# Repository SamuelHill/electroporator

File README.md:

# Electroporator PCB

Various PCB designs for a simple, versatile, and inexpensive electroporator. Inspiration and original design from [T. Bullman, et. al. 2015](https://onlinelibrary.wiley.com/doi/10.1111/dgd.12216). As stated in the paper:

> Electroporation is a useful technique to study gene function during development but its broad application is hampered due to the expensive equipment needed.

While I agree with this and the rest of the paper largely, I believe the design set forth is both cluttered and unnecessarily complicated. This is mainly due to the use of a breadboard (or PCB breadboard), and given the current capabilities and price point of manufacturing a custom PCB this seems the obvious place to start for simplification. To that end, I designed a simple PCB that also contains much of the needed information for construction and operation on the silkscreen. After successfully implementing and using the v.0 system, I also designed and am working on implementing a handful of v.1 boards.

The layout of this project is a series of nested KiCad projects for easy navigation within KiCad. To better show the functionality of the HE721A IC's - and add this product and footprint - I created a custom part (found in the parts folder). In the gerber folder is the compiled output of the v.0 board which has been printed, tested, and used successfully. As more of the designs are tested I will add more completed gerber files. The archive folder can be ignored as it just includes some attempts at having the LED output on the electrode side of the circuit. The v0 and v1 folders contain the designs for each version and v1 contains a number of modifications that are discussed later in this readme.

## Breadboard layout

To make sure I had the circuit correct and that my parts were compatible I did a test on a breadboard just as the paper laid out.

Breadboard build:

Testing with oscilloscope:

Sizing up PCB from breadboard layout:

## V.0 Design

Below are 2D and 3D renders of the v.0 design:

This board uses the same layout as the breadboard in terms of components and connections, but - due to the nature of PCBs - doesn't require extra wiring. While the parts listed in the paper are mostly generic and easy to come by such as the resistors, capacitors, and 555 timer, the reed relay is definitely a bit more of an unusual component. While not very expensive for the kind used here, it is unlikely you have a compatible IC lying around. Also, this is another change from the paper - albeit minor - in that the PCB is only designed for reed relays and not miniature latching relays. In addition to using reed relays, I am expecting a relay with diode protection. The relays I used for my testing and builds were [HE721A0510's](https://www.mouser.com/ProductDetail/Littelfuse/HE721A0510?qs=X8LBAgEWIKIfZjBxMXqqBA%3D%3D).

## V.1 Designs *(ordered components on wait lists - _IN PROGRESS & UNTESTED_)*

The v.0 system is reasonably simple and flexible (mostly due to the standard hole spacing for various IO connection types), but there are a few improvements I have thought of while building several v.0 electroporators. To start, all v.1 PCBs do not have a switch in the electrode side of the circuit as this was confusing and seems redundant. From here, I have made a JST connector only version as JST plugs are relatively low profile, dependable, and easy to install once setup. This replaces all screw terminals, buttons and switches, LED indicators, and potentiometer connections with JST plugs - making all IO consistently implemented.

The next v.1 iteration is a JST only copy with a more powerful current regulator in the form of a TL783. While previous versions were limited by the current regulator limitations, this version pushes further into the operational range for the reed relay and allows for pulse voltages from 1.25 to 125V. This opens up the ~45V - 125V range for systems that may require more power. To accommodate the adjust-ability of TL783 for regulating the current (I=Vref/R), R6 was beefed up to allow for radial resistors of appropriate values or a connection to appropriately spec'd potentiometers. These are the only modifications needed as the reed relay and JST connectors can already handle these voltages.

The JST only version could also be considered bloated if you know that your voltage is current regulated. If you were using a lab bench power supply with the current limited, the welding of the reeds in the relay should not be a concern. As such, I made a version with no current regulator for the most simple version of the circuit. This also opens up the full range of up to 200V for the relay so long as your power supply can handle those outputs limited to such low current values.

Lastly, in the interest of pushing the capabilities of this design, I created a kilo-volt version. At somewhere between 5x and 10x more expensive than the HE721, and with a > 1 year lead time, the [SHV05-1A85-78D4K](https://www.mouser.com/ProductDetail/MEDER-electronic-Standex/SHV05-1A85-78D4K?qs=3BE4VKEPqliBgklxw9NVYw%3D%3D) was my choice of overpowered reed relay for this electroporator. In addition to a bigger reed relay (no current regulation like above), the JST connectors won't cut it and have been replaced with kV compatible screw terminals.

## V.0 Implementations

Below are two of the implementations that went to be used in the Hill lab and have been tested on sponge cells. Imaging and further testing is ongoing.

### Large project box

#### Lid:

#### Sides:

#### Lid IO:

#### Sides IO:

#### IO Layout:

This is also the look of the final system (sans LED). The pulse trigger is a tattoo gun pedal so the electrodes can be positioned and operated by the users hands while the trigger can be done with your feet.

#### Power supply:

Yellow & black for 5V, red and black for variable power output...

#### Power IO:

Includes the LED for indicating when the pulse occurs...

IO with wires attached and organized...

Power IO removed from lid for next step...

#### PCB:

Power (5V and electrode variable), electrodes, and the electrode test button wiring...

Power switch, pulse duration potentiometer, and pulse LED indicator control wiring...

All PCB connections in place in box...

Cleaned up the lid wiring...

---

### Small project box

## Results

Using the large project box implementation in the lab with a set of adherent cell electrodes (pictured below):

Sponges (gemules adhered to some variety of 35mm glass bottom petri dish with a micro-well and cover glass) successfully electroporated with plasmids expressing GFP:

## Future work

Development of a SMT line of boards that can be both smaller and more cheaply assembled by the same sorts of PCB manufacturing facilities that allow for the cheaper custom PCBs used in this project. Many PCB production houses have assembly features wherein your board is not only printed but all available components are assembled onto the board for you. While through hole may be easier to do by hand, and is still needed for some IC's like the relay, SMT is cheaper to manufactur and assemble.

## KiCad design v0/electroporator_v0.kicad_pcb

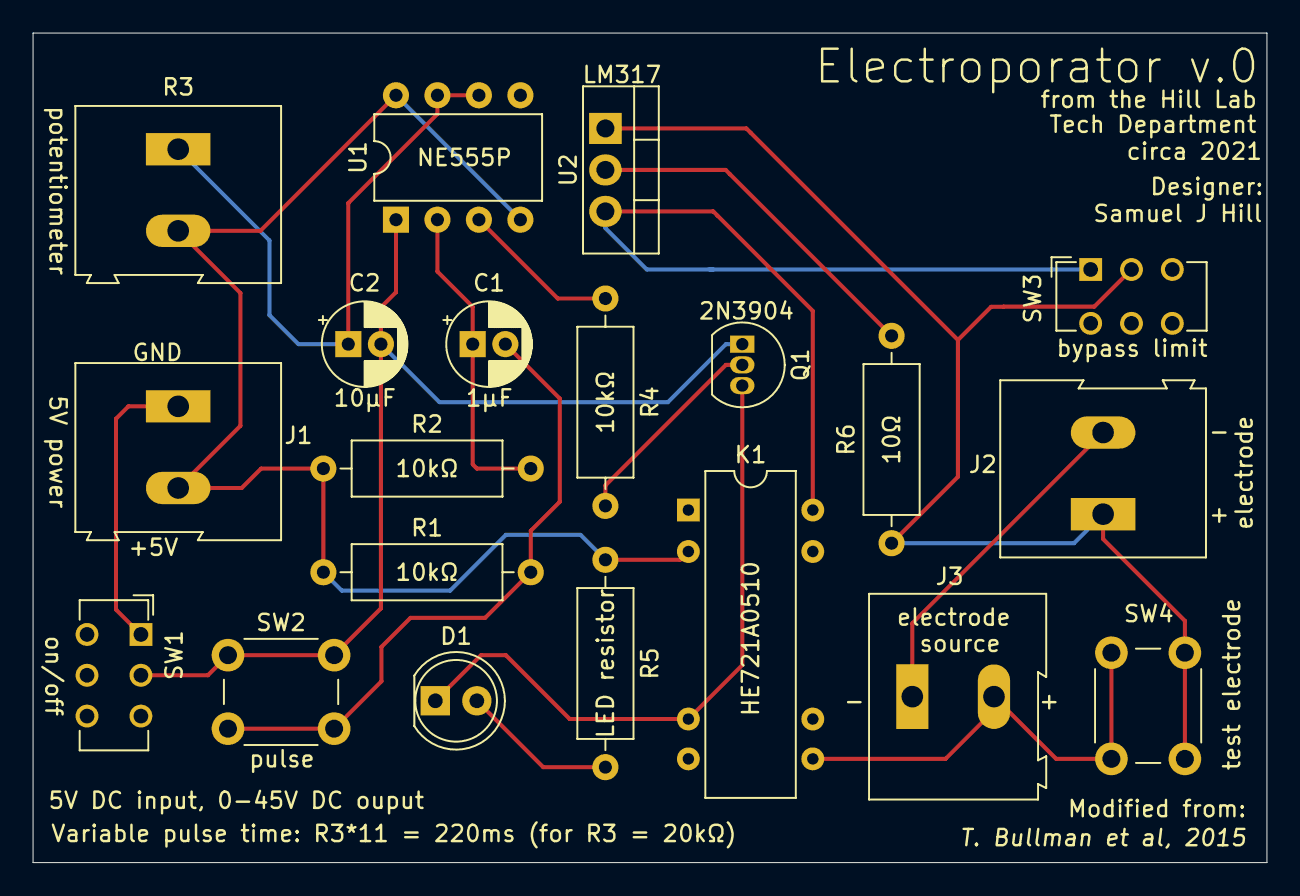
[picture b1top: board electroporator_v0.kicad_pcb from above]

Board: 2 copper layers, 75.6 x 50.8 mm, 20 parts (0 on the bottom side), 15 nets.

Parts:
C1: 1µF; CP_Radial_D5.0mm_P2.00mm
C2: 10µF; CP_Radial_D5.0mm_P2.00mm
D1: LED; LED_D5.0mm
J1: 5V Input; TerminalBlock_Altech_AK300-2_P5.00mm
J2: Electrodes Out; TerminalBlock_Altech_AK300-2_P5.00mm
J3: 0-45V Input; TerminalBlock_Altech_AK300-2_P5.00mm
K1: HE721A0510; Relay_StandexMeder_DIP_LowProfile
Q1: 2N3904; TO-92_Inline
R1, R2, R4: 10kΩ; R_Axial_DIN0309_L9.0mm_D3.2mm_P12.70mm_Horizontal
R3: 20kΩ Pot; TerminalBlock_Altech_AK300-2_P5.00mm
R5: 2kΩ; R_Axial_DIN0309_L9.0mm_D3.2mm_P12.70mm_Horizontal
R6: 10Ω; R_Axial_DIN0309_L9.0mm_D3.2mm_P12.70mm_Horizontal
SW1: On/Off; SW_CuK_JS202011CQN_DPDT_Straight
SW2: Pulse; SW_PUSH_6mm
SW3: Limiter Bypass; SW_CuK_JS202011CQN_DPDT_Straight
SW4: Test electrodes; SW_PUSH_6mm
U1: NE555P; DIP-8_W7.62mm
U2: LM317; TO-220-3_Vertical

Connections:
+5V: J1.2, K1.2, R1.1, R2.1, R3.2, R5.1, U1.4, U1.8
+VDC: J3.2, K1.8, SW4.1
-VDC: J2.2, J3.1
GND: J1.1, SW1.1
unnamed: C1.1, R2.2, U1.2
unnamed: C1.2, R1.2, SW2.2
unnamed: C2.1, R3.1, U1.6, U1.7
unnamed: C2.2, Q1.1, SW1.2, SW2.1, U1.1
unnamed: D1.1, K1.6, Q1.3
unnamed: D1.2, R5.2
unnamed: J2.1, R6.2, SW3.2, SW4.2, U2.1
unnamed: K1.14, SW3.1, U2.3
unnamed: Q1.2, R4.2
unnamed: R4.1, U1.3
unnamed: R6.1, U2.2

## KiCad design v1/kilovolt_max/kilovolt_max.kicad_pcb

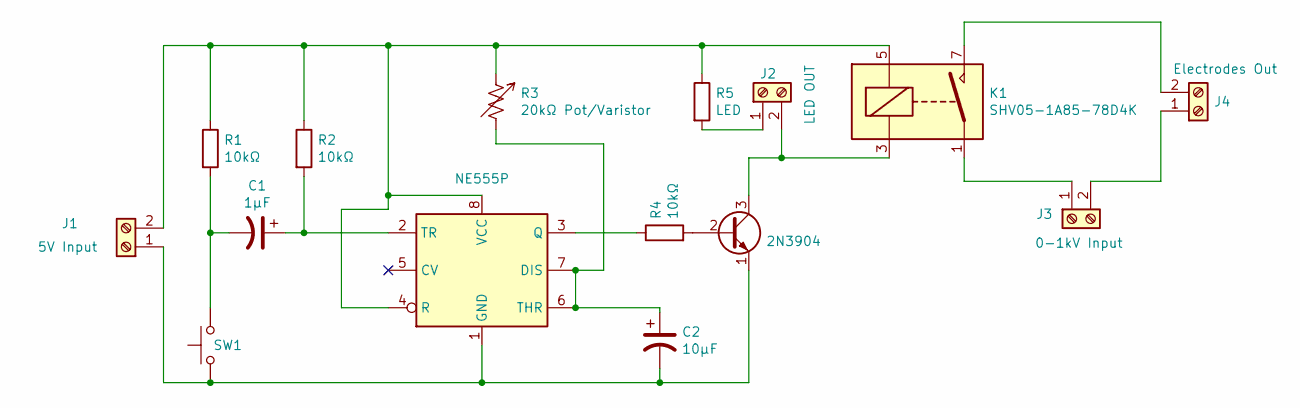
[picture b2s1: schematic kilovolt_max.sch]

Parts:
C1: 1µF; CP_Radial_D5.0mm_P2.00mm
C2: 10µF; CP_Radial_D5.0mm_P2.00mm
J1: 5V Input; JST_XH_B2B-XH-AM_1x02_P2.50mm_Vertical
J2: LED OUT; JST_XH_B2B-XH-AM_1x02_P2.50mm_Vertical
J3: 0-1kV Input; DIP-4_300
J4: Electrodes Out; DIP-4_300
K1: SHV05-1A85-78D4K; Relay_SPST_StandexMeder_SHV
Q1: 2N3904; TO-92_Inline
R1, R2, R4: 10kΩ; R_Axial_DIN0207_L6.3mm_D2.5mm_P10.16mm_Horizontal
R3: 20kΩ Pot/Varistor; JST_XH_B2B-XH-AM_1x02_P2.50mm_Vertical
R5: LED; R_Axial_DIN0207_L6.3mm_D2.5mm_P10.16mm_Horizontal
SW1: Pulse; JST_XH_B2B-XH-AM_1x02_P2.50mm_Vertical
U1: NE555P; DIP-8_W7.62mm

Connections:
unnamed: C1.1, R2.2, U1.2 (TR)
unnamed: C1.2, R1.2, SW1.2
unnamed: C2.1, R3.2, U1.6 (THR), U1.7 (DIS)
unnamed: C2.2, J1.1, Q1.1 (E), SW1.1, U1.1 (GND)
unnamed: J1.2, K1.5, R1.1, R2.1, R3.1, R5.1, U1.4 (R), U1.8 (VCC)
unnamed: J2.1, R5.2
unnamed: J2.2, K1.3, Q1.3 (C)
unnamed: J3.1, K1.1
unnamed: J3.2, J4.1
unnamed: J4.2, K1.7
unnamed: Q1.2 (B), R4.2
unnamed: R4.1, U1.3 (Q)

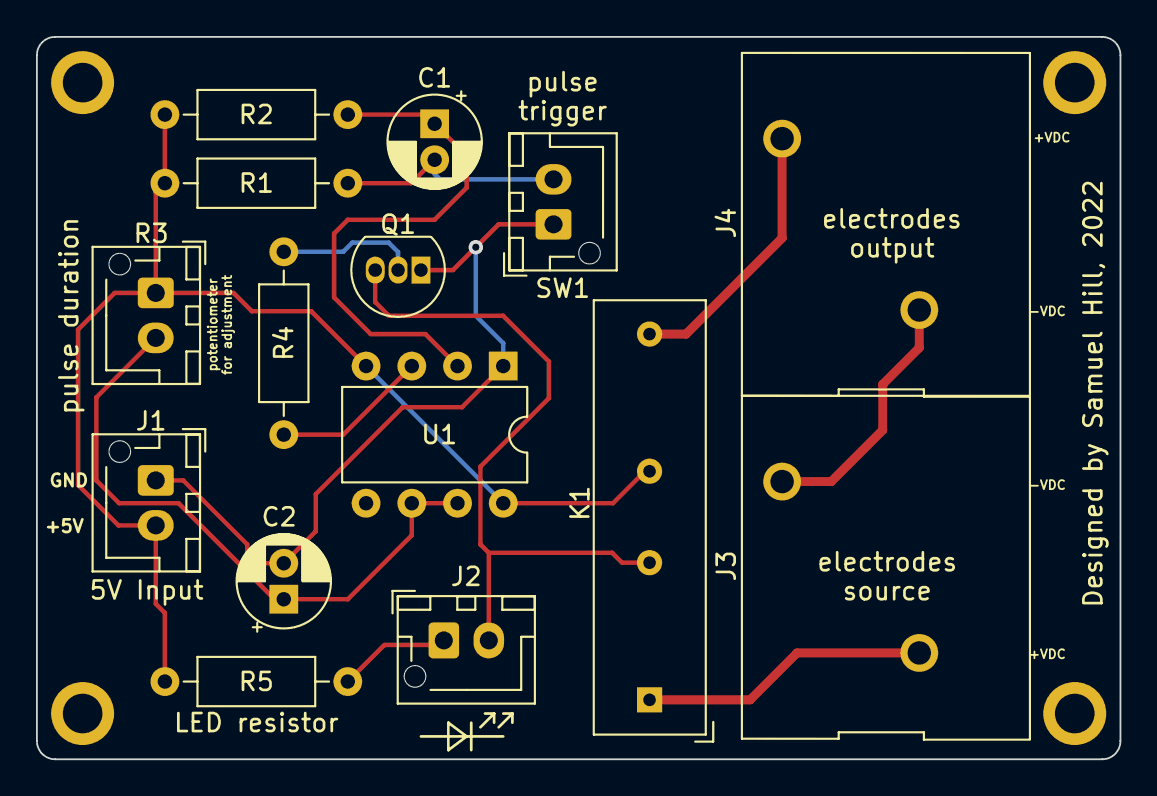
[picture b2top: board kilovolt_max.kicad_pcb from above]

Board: 2 copper layers, 60.2 x 40.1 mm, 15 parts (0 on the bottom side), 12 nets.

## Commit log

2022-08-27 Updated readme with images
2022-08-27 moved kV image to the proper location
2022-08-27 Added results to readme
